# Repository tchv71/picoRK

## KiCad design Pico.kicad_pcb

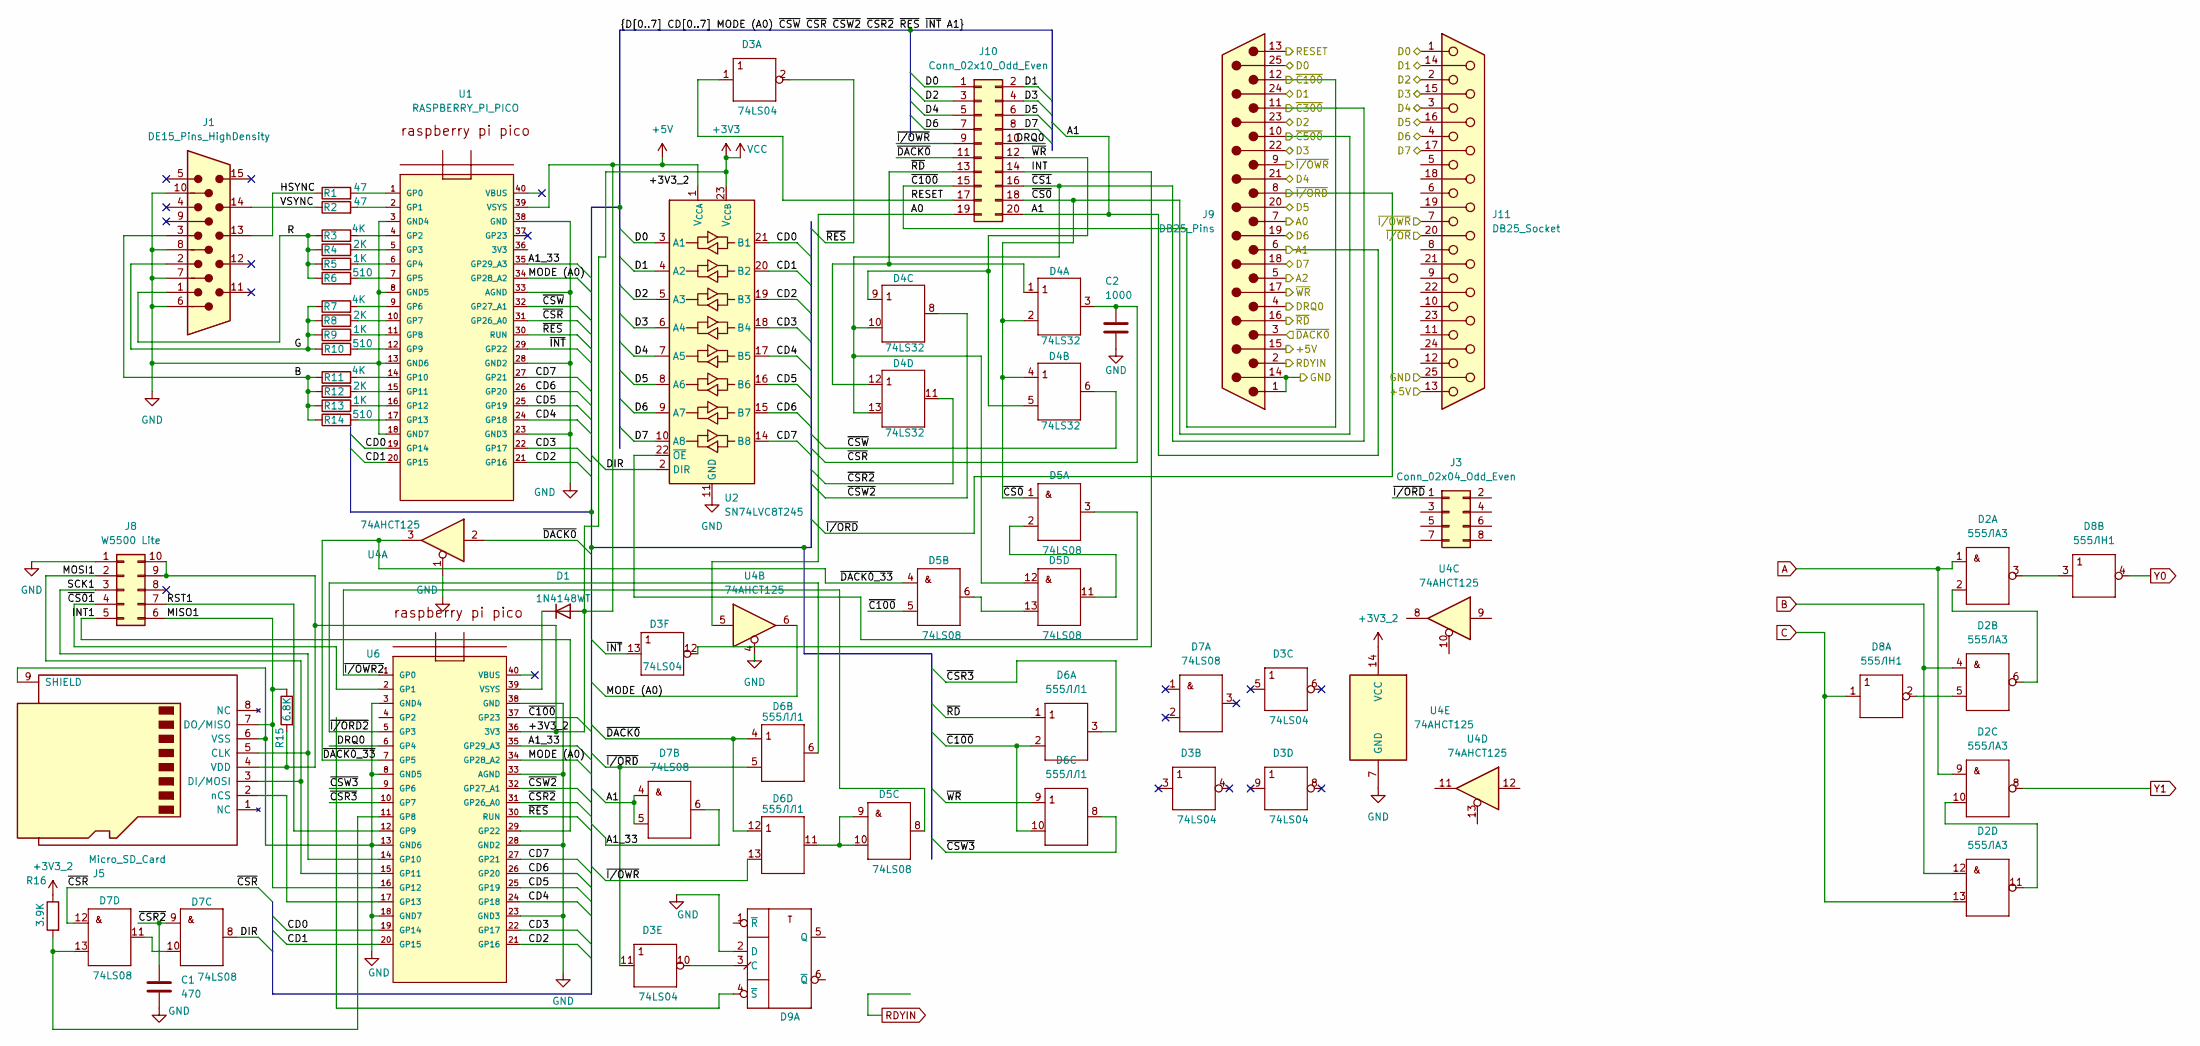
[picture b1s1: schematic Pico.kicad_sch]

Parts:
C1: 470; C_Rect_L7.0mm_W2.0mm_P5.00mm
C2: 1000; C_Rect_L7.0mm_W2.0mm_P5.00mm
D1: 1N4148WT; D_SOD-523
D2: 133LA3; DIP-14_W7.62mm
D3, D8: 133LN1; DIP-14_W7.62mm
D4: `; DIP-14_W7.62mm
D5, D7: 133LI1; DIP-14_W7.62mm
D6: 133LL1; DIP-14_W7.62mm
D9: 74HC74N; DIP-14_W7.62mm_Socket
J1: DE15_Pins_HighDensity; DSUB-15-HD_Pins_Horizontal_P2.29x1.90mm_EdgePinOffset3.03mm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
J3: Conn_02x04_Odd_Even; PinHeader_2x04_P2.54mm_Vertical
J5: Micro_SD_Card; microSD_HC_Wuerth_693072010801
J8: W5500 Lite; Wuerth_WR-PHD_613010216921_Large_2x05_P2.54mm_Vertical
J9: DB25_Pins
J10: Conn_02x10_Odd_Even; PinHeader_2x10_P2.54mm_Vertical
J11: DB25_Socket
R1, R2: 47; R_Axial_DIN0207_L6.3mm_D2.5mm_P5.08mm_Vertical
R3, R7, R11: 4K; R_Axial_DIN0207_L6.3mm_D2.5mm_P5.08mm_Vertical
R4, R8, R12: 2K; R_Axial_DIN0207_L6.3mm_D2.5mm_P5.08mm_Vertical
R5, R9, R13: 1K; R_Axial_DIN0207_L6.3mm_D2.5mm_P5.08mm_Vertical
R6, R10, R14: 510; R_Axial_DIN0207_L6.3mm_D2.5mm_P5.08mm_Vertical
R15: 6.8K; R_Axial_DIN0207_L6.3mm_D2.5mm_P5.08mm_Vertical
R16: 3.9K; R_Axial_DIN0207_L6.3mm_D2.5mm_P5.08mm_Vertical
U1, U6: RASPBERRY_PI_PICO; RaspberryPi_Pico_Common_THT
U2: SN74LVC8T245; DIP-24_18.0mmx34.29mm_W15.24mm
U4: 74AHCT125; TSSOP-14_4.4x5mm_P0.65mm

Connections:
+3V3: D1.2 (A), D2.14 (VCC), D3.14 (VCC), D4.14 (VCC), D5.14 (VCC), D6.14 (VCC), D7.14 (VCC), D8.14 (VCC), D9.14 (VCC), J5.4 (VDD), J8.9, J8.10, R15.2, R16.1, U1.39 (VSYS), U2.1 (V_{CCA}), U2.23 (V_{CCB}), U2.24 (V_{CCB}), U4.14 (VCC), U6.36 (3V3)
/A0: J10.19, U4.5
/A1: D7.4 (A), D7.5 (B), J10.20
/A1_33: D7.6 (Y), U1.35 (GP29_A3), U6.35 (GP29_A3)
/CD0: U1.19 (GP14), U2.21 (B1), U6.19 (GP14)
/CD1: U1.20 (GP15), U2.20 (B2), U6.20 (GP15)
/CD2: U1.21 (GP16), U2.19 (B3), U6.21 (GP16)
/CD3: U1.22 (GP17), U2.18 (B4), U6.22 (GP17)
/CD4: U1.24 (GP18), U2.17 (B5), U6.24 (GP18)
/CD5: U1.25 (GP19), U2.16 (B6), U6.25 (GP19)
/CD6: U1.26 (GP20), U2.15 (B7), U6.26 (GP20)
/CD7: U1.27 (GP21), U2.14 (B8), U6.27 (GP21)
/D0: J10.1, U2.3 (A1)
/D1: J10.2, U2.4 (A2)
/D2: J10.3, U2.5 (A3)
/D3: J10.4, U2.6 (A4)
/D4: J10.5, U2.7 (A5)
/D5: J10.6, U2.8 (A6)
/D6: J10.7, U2.9 (A7)
/D7: J10.8, U2.10 (A8)
/DIR: D7.8 (Y), U2.2 (DIR)
/DRQ0: D9.4 (~S), J10.10, U6.6 (GP4)
/G: J1.2, R7.1, R8.1, R9.1, R10.1
/HSYNC: J1.13, R1.1
/INT: D3.12 (Y), J10.14
/INT1: J8.5, U6.29 (GP22)
/MISO1: J5.7 (DO/MISO), J8.6, R15.1, U6.16 (GP12)
/MODE (A0): U1.34 (GP28_A2), U4.6, U6.34 (GP28_A2)
/MOSI1: J5.3 (DI/MOSI), J8.2, U6.15 (GP11)
/R: J1.1, R3.1, R4.1, R5.1, R6.1
/RESET: D3.1 (A), J10.17
/RST1: J8.7, U6.12 (GP9)
/SCK1: J5.5 (CLK), J8.3, U6.14 (GP10)
/VSYNC: J1.14, R2.1
/~C100: D5.5 (B), D6.2 (B), D6.10 (B), J9.12, J10.15, U6.37 (GP23)
/~CS0: D4.2 (B), D4.4 (A), D5.1 (A), J9.10, J10.18
/~CS1: D4.10 (B), D4.13 (B), D5.12 (A), J9.11, J10.16
/~CS01: J8.4, U6.2 (GP1)
/~CSR2: C1.1, D4.11 (Y), D7.9 (A), U6.31 (GP26_A0)
/~CSR3: D6.3 (Y), U6.10 (GP7)
/~CSR: C2.1, D4.3 (Y), D7.12 (A), U1.31 (GP26_A0)
/~CSW2: D4.8 (Y), U6.32 (GP27_A1)
/~CSW3: D6.8 (Y), U6.9 (GP6)
/~CSW: D4.6 (Y), U1.32 (GP27_A1)
/~DACK0_33: D5.4 (A), U4.3, U6.7 (GP5)
/~DACK0: D6.4 (A), D6.12 (A), J10.11, U4.2
/~INT: D3.13 (A), U1.29 (GP22)
/~I/ORD2: D6.6 (Y), U6.5 (GP3)
/~I/ORD: D3.11 (A), D6.5 (B), J3.1, J9.8
/~I/OWR2: D5.8 (Y), U6.1 (GP0)
/~I/OWR: D6.13 (B), J10.9
/~RD: D4.1 (A), D4.12 (A), D6.1 (A), J10.13
/~RES: D3.2 (Y), U1.30 (RUN), U6.30 (RUN)
/~WR: D4.5 (B), D4.9 (A), D6.9 (A), J10.12
A: D2.1 (A), D2.9 (A)
B: D2.4 (A), D2.12 (A), J1.3, R11.1, R12.1, R13.1, R14.1
C: D2.13 (B), D8.1 (A)
GND: C1.2, C2.2, D2.7 (GND), D3.7 (GND), D4.7 (GND), D5.7 (GND), D6.7 (GND), D7.7 (GND), D8.7 (GND), D9.2 (D), D9.7 (GND), J1.6, J1.7, J1.8, J1.10, J5.6 (VSS), J5.9 (SHIELD), J8.1, U1.3 (GND4), U1.8 (GND5), U1.13 (GND6), U1.18 (GND7), U1.23 (GND3), U1.28 (GND2), U1.33 (AGND), U1.38 (GND), U2.11 (GND), U2.12 (GND), U2.13 (GND), U4.1, U4.4, U4.7 (GND), U6.3 (GND4), U6.8 (GND5), U6.13 (GND6), U6.18 (GND7), U6.23 (GND3), U6.28 (GND2), U6.33 (AGND), U6.38 (GND)
unnamed: D1.1 (K), U6.39 (VSYS)
unnamed: D2.2 (B), D2.6 (Y)
unnamed: D2.3 (Y), D8.3 (A)
unnamed: D2.5 (B), D8.2 (Y)
unnamed: D2.10 (B), D2.11 (Y)
unnamed: D3.10 (Y), D9.3 (C)
unnamed: D5.2 (B), D5.11 (Y)
unnamed: D5.3 (Y), U2.22 (~OE)
unnamed: D5.6 (Y), D5.13 (B)
unnamed: D5.9 (A), D5.10 (B), D6.11 (Y)
unnamed: D7.10 (B), D7.11 (Y)
unnamed: D7.13 (B), R16.2, U6.11 (GP8)
unnamed: J5.2 (nCS), U6.17 (GP13)
unnamed: J9.25, J11.1
unnamed: J9.23, J11.2
unnamed: J9.21, J11.3
unnamed: J9.19, J11.4
unnamed: J9.9, J11.7
unnamed: J9.15, J11.13
unnamed: J9.24, J11.14
unnamed: J9.22, J11.15
unnamed: J9.20, J11.16
unnamed: J9.18, J11.17
unnamed: J9.1, J9.14, J11.25
unnamed: R1.2, U1.1 (GP0)
unnamed: R2.2, U1.2 (GP1)
unnamed: R3.2, U1.4 (GP2)
unnamed: R4.2, U1.5 (GP3)
unnamed: R5.2, U1.6 (GP4)
unnamed: R6.2, U1.7 (GP5)
unnamed: R7.2, U1.9 (GP6)
unnamed: R8.2, U1.10 (GP7)
unnamed: R9.2, U1.11 (GP8)
unnamed: R10.2, U1.12 (GP9)
unnamed: R11.2, U1.14 (GP10)
unnamed: R12.2, U1.15 (GP11)
unnamed: R13.2, U1.16 (GP12)
unnamed: R14.2, U1.17 (GP13)
Y0: D8.4 (Y)
Y1: D2.8 (Y)

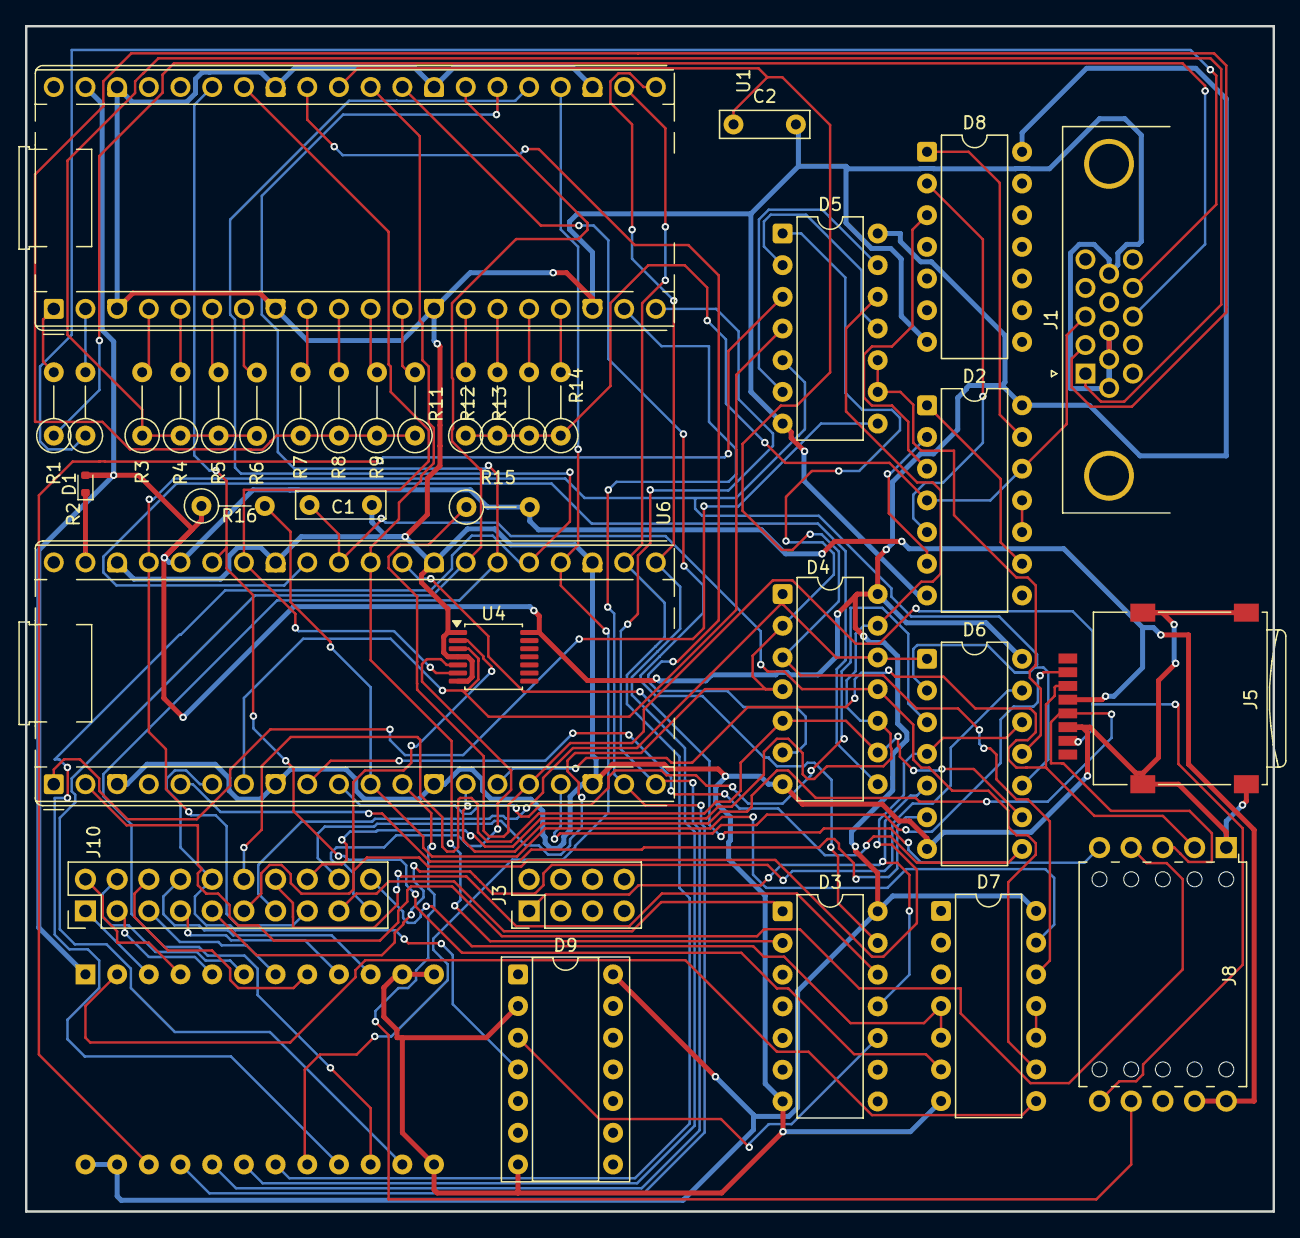
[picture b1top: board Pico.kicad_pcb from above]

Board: 2 copper layers, 100.0 x 95.0 mm, 36 parts (1 on the bottom side), 85 nets.

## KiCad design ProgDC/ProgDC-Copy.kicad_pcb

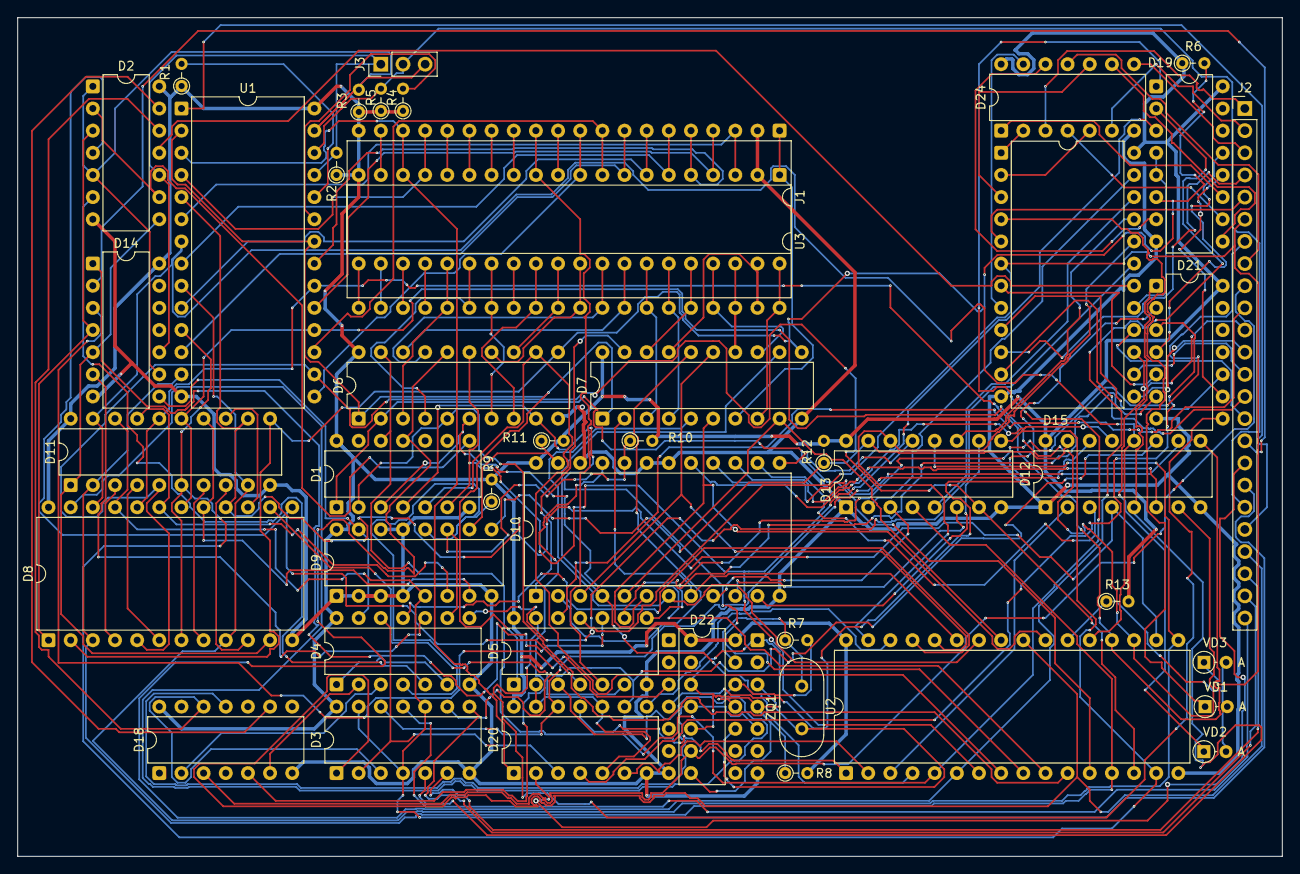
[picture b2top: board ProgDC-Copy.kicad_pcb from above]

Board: 2 copper layers, 145.0 x 96.2 mm, 45 parts (1 on the bottom side), 171 nets.

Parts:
D1: K155LA2; DIP-14_W7.62mm
D2, D4: 133LL1; DIP-14_W7.62mm
D3, D20, D24: 133LI1; DIP-14_W7.62mm
D5, D22: 133LN1; DIP-14_W7.62mm
D6, D7, D11: 1533IR22; DIP-20_W7.62mm
D8: K589IR12; DIP-24_W15.24mm
D9: KR556RT4; DIP-16_W7.62mm
D10: KR537RU10; DIP-24_W15.24mm
D12, D13: K589AP16; DIP-16_W7.62mm
D14: 133LA3; DIP-14_W7.62mm
D15: 155ID3; DIP-24_W15.24mm
D18: 133TM2; DIP-14_W7.62mm
D19: 74AC138(COMB); DIP-16_W7.62mm
D21: 74HC86N; DIP-14_W7.62mm
D23: 74AC74N; DIP-14_W7.62mm
J1: Conn_02x20_Counter_Clockwise_MountingPin; DIP-40_W15.24mm
J2: Conn_01x24_Pin; PinHeader_1x24_P2.54mm_Vertical
J3: Conn_01x03_Pin; PinHeader_1x03_P2.54mm_Vertical
R1, R2, R3, R4, R5, R6, R9, R10, R11, R12, R13: R0125; R_Axial_DIN0204_L3.6mm_D1.6mm_P2.54mm_Vertical
R7, R8: R0125H; R_Axial_DIN0204_L3.6mm_D1.6mm_P2.54mm_Vertical
U1: KR580VK28; DIP-28_W15.24mm
U2: 628512; DIP-32_W15.24mm
U3: CPU; DIP-40_W15.24mm
VD1, VD2, VD3: 1N4148; D_DO-34_SOD68_P2.54mm_Vertical_AnodeUp
ZQ1: QUARTZ; Crystal_HC18-U_Vertical

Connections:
+5V: D1.14 (VCC), D2.14 (VCC), D3.14 (VCC), D4.14 (VCC), D5.14 (VCC), D6.20 (VCC), D7.20 (VCC), D8.24 (VCC), D9.16 (+5V), D10.24 (VCC), D11.20 (VCC), D12.16 (VCC), D13.16 (VCC), D14.14 (VCC), D15.24 (VCC), D18.14 (VCC), D19.16 (VCC), D20.14 (VCC), D21.14 (VCC), D22.14 (VCC), D23.14 (VCC), D24.14 (VCC), J1.20, R1.1 (TOP), R2.1 (TOP), R3.1 (TOP), R4.1 (TOP), R5.1 (TOP), R6.1 (TOP), R8.2, R9.2 (BOT), R10.2 (BOT), R11.2 (BOT), R12.2 (BOT), R13.2 (BOT), U1.28 (VCC), U2.32 (VCC), U3.20 (VCC)
/8MHZ: D18.11 (C), D23.5 (Q), D23.11 (C)
/"1": D6.11 (PE), D7.11 (PE), D8.2 (MD), D11.11 (PE), D19.6 (E1), R6.2 (BOT)
/+12V: J1.28, U3.28 (+12V)
/-5V: J1.11, U3.11 (-5V)
/A0: D6.3 (D0), J1.25, U3.25 (A0)
/A1: D6.4 (D1), J1.26, U3.26 (A1)
/A2: D6.7 (D2), J1.27, U3.27 (A2)
/A3: D6.8 (D3), J1.29, U3.29 (A3)
/A4: D6.13 (D4), J1.30, U3.30 (A4)
/A5: D6.14 (D5), J1.31, U3.31 (A5)
/A6: D6.17 (D6), J1.32, U3.32 (A6)
/A7: D6.18 (D7), J1.33, U3.33 (A7)
/A8: D7.3 (D0), J1.34, U3.34 (A8)
/A9: D7.4 (D1), J1.35, U3.35 (A9)
/A10: D7.7 (D2), J1.1, U3.1 (A10)
/A11: D7.8 (D3), J1.40, U3.40 (A11)
/A12: D7.13 (D4), J1.37, U3.37 (A12)
/A13: D7.14 (D5), J1.38, U3.38 (A13)
/A14: D7.17 (D6), J1.39, U3.39 (A14)
/A15: D7.18 (D7), J1.36, U3.36 (A15)
/AB0: D1.1, D6.2 (Q0), U2.12 (A0)
/AB1: D1.2, D6.5 (Q1), U2.11 (A1)
/AB2: D1.3, D6.6 (Q2), U2.10 (A2)
/AB3: D1.4, D6.9 (Q3), U2.9 (A3)
/AB4: D1.5, D6.12 (Q4), U2.8 (A4)
/AB5: D1.6, D6.15 (Q5), D19.3 (2), U2.7 (A5)
/AB6: D1.11, D6.16 (Q6), D19.2 (1), U2.6 (A6)
/AB7: D1.12, D6.19 (Q7), D19.1 (0), U2.5 (A7)
/AB8: D7.2 (Q0), D10.8 (A10), U2.27 (A8)
/AB9: D7.5 (Q1), D10.7 (A9), U2.26 (A9)
/AB10: D7.6 (Q2), D10.6 (A8), U2.23 (A10)
/AB11: D7.9 (Q3), D10.5 (A7), U2.25 (A11)
/AB12: D7.12 (Q4), D10.4 (A6), U2.4 (A12)
/AB13: D7.15 (Q5), D10.3 (A5), U2.28 (A13)
/AB14: D7.16 (Q6), D10.2 (A4)
/AB15: D7.19 (Q7), D10.1 (A3)
/ARR16: D20.6 (Y), U2.2 (A16)
/ARR17: D20.8 (Y), U2.30 (A17)
/ARR18: D20.11 (Y), U2.1 (A18)
/C1: J1.22, U3.22 (C1)
/C2: J1.15, U3.15 (C2)
/C800_VI53_2: D5.13 (A), D21.8 (Y)
/CLK: D18.3 (C), D23.9 (Q), J2.9
/D0: J1.10, U1.15 (D0), U3.10 (D0)
/D1: J1.9, U1.17 (D1), U3.9 (D1)
/D2: J1.8, U1.12 (D2), U3.8 (D2)
/D3: J1.7, U1.10 (D3), U3.7 (D3)
/D4: J1.3, U1.6 (D4), U3.3 (D4)
/D5: J1.4, U1.19 (D5), U3.4 (D5)
/D6: J1.5, U1.21 (D6), U3.5 (D6)
/D7: J1.6, U1.8 (D7), U3.6 (D7)
/DB0: D8.3 (D0), D11.2 (Q0), D13.4 (DI0), U1.13 (DB0), U2.13 (D0)
/DB1: D8.5 (D1), D11.5 (Q1), D13.7 (DI1), U1.16 (DB1), U2.14 (D1)
/DB2: D8.7 (D2), D11.6 (Q2), D13.9 (DI2), U1.11 (DB2), U2.15 (D2)
/DB3: D8.9 (D3), D11.9 (Q3), D13.12 (DI3), U1.9 (DB3), U2.17 (D3)
/DB4: D8.16 (D4), D11.12 (Q4), D12.4 (DI0), U1.5 (DB4), U2.18 (D4)
/DB5: D8.18 (D5), D11.15 (Q5), D12.7 (DI1), U1.18 (DB5), U2.19 (D5)
/DB6: D8.20 (D6), D11.16 (Q6), D12.9 (DI2), U1.20 (DB6), U2.20 (D6)
/DB7: D8.22 (D7), D11.19 (Q7), D12.12 (DI3), U1.7 (DB7), U2.21 (D7)
/DBIN: J1.17, U1.4 (DBIN), U3.17 (RC)
/HLD: J1.13, U3.13 (HLD)
/HLDA: D5.1 (A), D6.1 (~EO), D7.1 (~EO), U1.2 (HLDA), U1.22 (BUSEN)
/INT: J1.14, U3.14 (INT)
/INTE: J1.16, U3.16 (INTE)
/P0: D4.4 (A), D9.12 (D0), R9.1 (TOP)
/P1: D4.9 (A), D9.11 (D1), D10.20 (~OE), R10.1 (TOP)
/P2: D9.10 (D2), D10.23 (A2), R11.1 (TOP)
/P3: D9.9 (D3), D12.15 (~CE), D13.15 (~CE), R12.1 (TOP)
/Q0: D8.4 (Q0), D11.3 (D0)
/Q1: D8.6 (Q1), D11.4 (D1)
/Q2: D8.8 (Q2), D11.7 (D2)
/Q3: D8.10 (Q3), D11.8 (D3)
/Q4: D8.15 (Q4), D11.13 (D4)
/Q5: D8.17 (Q5), D9.7 (A2), D11.14 (D5)
/Q6: D8.19 (Q6), D9.6 (A1), D11.17 (D6)
/Q7: D3.4 (A), D3.10 (B), D3.13 (B), D8.21 (Q7), D9.5 (A0), D11.18 (D7), J2.18
/R0: D13.2 (DO0), D15.23 (1)
/R1: D13.5 (DO1), D15.22 (2)
/R2: D13.11 (DO2), D15.21 (4)
/R3: D13.14 (DO3), D15.20 (8), U2.31 (A15)
/R4: D12.2 (DO0), U2.3 (A14)
/R5: D3.5 (B), D12.5 (DO1), D21.1 (A)
/R6: D3.9 (A), D12.11 (DO2), D20.9 (A)
/R7: D3.12 (A), D12.14 (DO3), D20.12 (A)
/R8: D14.3 (Y), D22.3 (A)
/RAM_SEL: D14.2 (B), J2.16
/RDY: J1.23, U3.23 (RDY)
/RESET: D5.5 (A), J1.12, U3.12 (RST)
/ROM_A13: D3.6 (Y), J2.22
/ROM_A14: D3.8 (Y), J2.23
/ROM_A15: D3.11 (Y), J2.24
/STSTB: J2.20, U1.1 (STSTB)
/SYN: J1.19, U3.19 (SYN)
/WI: J1.24, U3.24 (WI)
/_HLDA: J1.21, U3.21 (HLDA)
/~C100_SD_CNTR: D15.10 (9), J2.4
/~C200_PPI1_: D24.3 (Y), J2.1
/~C200_PPI1: D15.1 (0), D24.2 (B)
/~C300: D15.14 (12), J2.13
/~C400_PPI2_: D24.6 (Y), J2.2
/~C400_PPI2: D15.2 (1), D24.5 (B)
/~C800_VI53_2_: D5.12 (Y), J2.10
/~C800_VI53_2: D15.9 (8), D21.10 (B)
/~CA00_PPI3: D15.16 (14), J2.15
/~CC00_VI53_1_: D5.8 (Y), J2.7
/~CC00_VI53_1: D15.7 (6), D21.5 (B)
/~CE00: D15.13 (11), J2.12
/~CS_628512: R13.1 (TOP), U2.22 (CS), VD1.2 (A), VD2.2 (A), VD3.2 (A)
/~CS_D800: D15.11 (10), J2.14
/~CS_DMA_: D24.11 (Y), J2.8
/~CS_DMA: D15.8 (7), D24.13 (B)
/~CS_RAMR: D15.4 (3), VD1.1 (K)
/~CS_ROM: D15.5 (4), J2.5
/~CS_SRAM_8000: D15.15 (13), J2.11, VD2.1 (K)
/~CS_VG75_: D24.8 (Y), J2.3
/~CS_VG75: D15.3 (2), D24.10 (B)
/~D15_CS1: D4.8 (Y), D15.19 (&C)
/~D15_CS2: D2.11 (Y), D15.18 (C)
/~F700: D15.17 (15), D19.4 (~E2), D19.5 (~E3)
/~INTA: R4.2 (BOT), U1.23 (INTA)
/~I/OR: D2.10 (B), D14.10 (B), J3.1, R2.2 (BOT), U1.25 (I/OR)
/~I/OW: D2.1 (A), D2.5 (B), D14.9 (A), J3.3, R3.2 (BOT), U1.27 (I/OW)
/~MEMR: R1.2 (BOT), U1.24 (MEMR)
/~MEMW_VT57: D20.2 (B), J2.17
/~MEMW: J2.19, J3.2, R5.2 (BOT), U1.26 (MEMW)
/~MWR: D3.2 (B), D4.12 (A), D20.3 (Y)
/~RAM_MAIN: D5.11 (A), D15.6 (5), J2.6, VD3.1 (K)
/~RD: D3.1 (A), J2.21, U2.24 (RD)
/~RESET: D5.6 (Y), D8.14 (RES)
/~WE_628512: D4.11 (Y), U2.29 (WR)
/~WR: D20.1 (A), J1.18, U1.3 (WR), U3.18 (TR)
GND: D1.7 (GND), D2.7 (GND), D3.7 (GND), D4.7 (GND), D5.7 (GND), D6.10 (GND), D7.10 (GND), D8.12 (GND), D9.1 (A6), D9.2 (A5), D9.3 (A4), D9.4 (A3), D9.8 (GND), D9.13 (~CS1), D9.14 (~CS2), D10.12 (GND), D10.18 (~CS), D10.19 (A0), D10.22 (A1), D11.10 (GND), D12.1 (~CS), D12.8 (GND), D13.1 (~CS), D13.8 (GND), D14.7 (GND), D15.12 (GND), D18.7 (GND), D19.8 (GND), D20.7 (GND), D21.7 (GND), D22.7 (GND), D23.7 (GND), D24.7 (GND), J1.2, U1.14 (GND), U2.16 (GND), U3.2 (GND)
unnamed: D1.8, D2.2 (B), D2.9 (A)
unnamed: D2.4 (A), D5.4 (Y), D8.13 (CS2)
unnamed: D2.6 (Y), D4.5 (B)
unnamed: D4.1 (A), D4.6 (Y)
unnamed: D5.3 (A), D8.23 (S1)
unnamed: D10.9 (D0), D13.3 (DB0)
unnamed: D10.10 (D1), D13.6 (DB1)
unnamed: D10.11 (D2), D13.10 (DB2)
unnamed: D10.13 (D3), D13.13 (DB3)
unnamed: D10.14 (D4), D12.3 (DB0)
unnamed: D10.15 (D5), D12.6 (DB1)
unnamed: D10.16 (D6), D12.10 (DB2)
unnamed: D10.17 (D7), D12.13 (DB3)
unnamed: D10.21 (~WE), D18.5 (Q)
unnamed: D2.8 (Y), D8.11 (EV), D11.1 (~EO), D14.5 (B)
unnamed: D5.10 (Y), D14.1 (A)
unnamed: D2.3 (Y), D8.1 (CS1), D14.4 (A)
unnamed: D4.10 (B), D14.6 (Y)
unnamed: D4.13 (B), D9.15 (A7), D14.8 (Y)
unnamed: D4.3 (Y), D18.2 (D)
unnamed: D4.2 (B), D18.6 (~Q)
unnamed: D2.12 (A), D3.3 (Y), D18.12 (D)
unnamed: D2.13 (B), D18.9 (Q)
unnamed: D19.12 (3), D21.9 (A)
unnamed: D19.11 (4), D24.1 (A)
unnamed: D19.10 (5), D24.4 (A)
unnamed: D19.9 (6), D24.9 (A)
unnamed: D20.4 (A), D21.3 (Y)
unnamed: D5.2 (Y), D20.5 (B), D20.10 (B), D20.13 (B)
unnamed: D21.2 (B), D22.4 (Y)
unnamed: D19.13 (2), D21.4 (A)
unnamed: D5.9 (A), D21.6 (Y)
unnamed: D22.11 (A), D22.12 (Y), R7.2
unnamed: D22.10 (Y), D23.3 (C), ZQ1.1
unnamed: D22.13 (A), R7.1, ZQ1.2
unnamed: D23.2 (D), D23.6 (~Q)
unnamed: D23.1 (~R), D23.4 (~S), D23.8 (~Q), D23.10 (~S), D23.12 (D), R8.1
unnamed: D19.7, D24.12 (A)

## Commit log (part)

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2026-02-04 Add
    Add
2026-02-05 Fix PCB
2026-02-07 1
    1
2026-04-06 Fix bugs
2026-04-23 Add PicoPDC
